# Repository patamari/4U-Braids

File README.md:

4U port of Braids, hardware is CC-by-SA 3.0.

C24 should be a good bipolar 10uF electrolytic cap.

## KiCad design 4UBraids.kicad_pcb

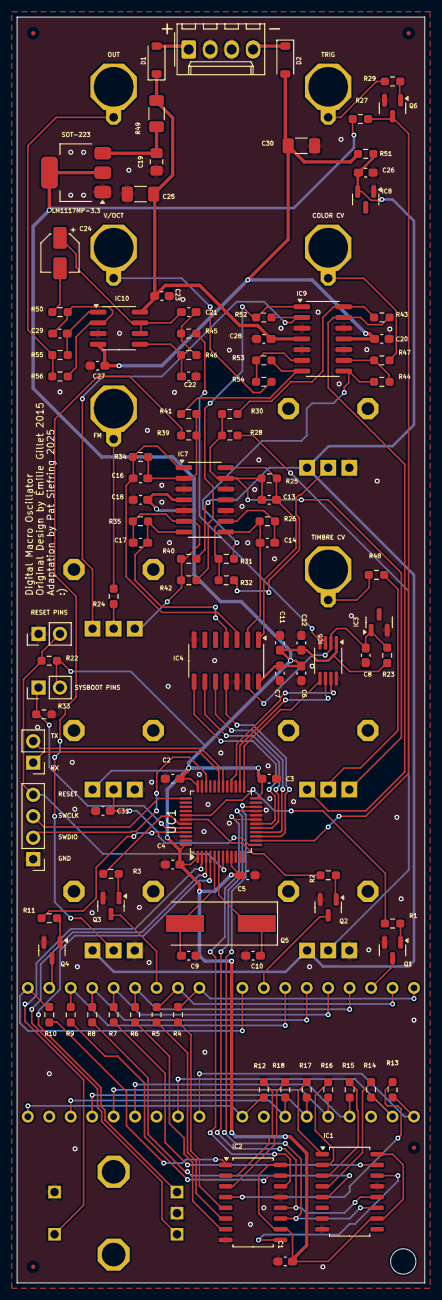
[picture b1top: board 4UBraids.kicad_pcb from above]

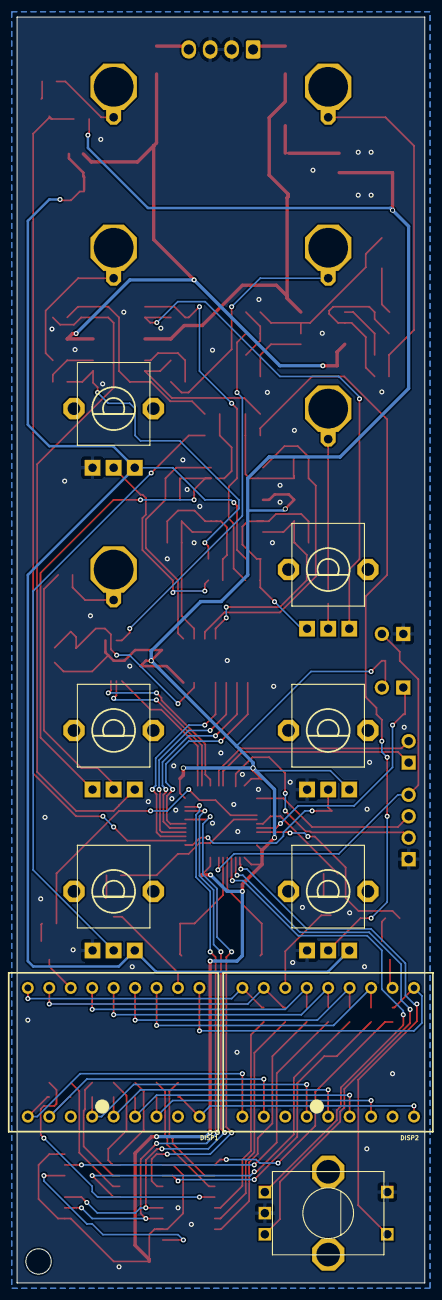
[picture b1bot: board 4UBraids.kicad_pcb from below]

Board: 2 copper layers, 48.3 x 149.9 mm, 108 parts (9 on the bottom side), 97 nets.

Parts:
C1, C2, C3, C4, C5, C7, C11, C18, C20, C23, C26, C27, C28, C31: 100n; C_0603_1608Metric_Pad1.08x0.95mm_HandSolder
C6, C12: 1u; C_0603_1608Metric_Pad1.08x0.95mm_HandSolder
C8: 470n; C_0603_1608Metric_Pad1.08x0.95mm_HandSolder
C9, C10: 18p; C_0603_1608Metric_Pad1.08x0.95mm_HandSolder
C13, C14, C16, C17: 1n; C_0603_1608Metric_Pad1.08x0.95mm_HandSolder
C19: 22uF; C_0805_2012Metric_Pad1.18x1.45mm_HandSolder
C21, C22: 100p; C_0603_1608Metric_Pad1.08x0.95mm_HandSolder
C24: 10u; CP_Elec_4x5.4
C25, C30: 47uF; C_1206_3216Metric_Pad1.33x1.80mm_HandSolder
C29: 47p; C_0603_1608Metric_Pad1.08x0.95mm_HandSolder
D1, D2: 1N5819HW; D_SOD-123
DISP1, DISP2: KINGBRIGHT-PDC54-11; PDC54
IC1, IC2: 74HC595D; SOIC-16_4.55x10.3mm_P1.27mm
IC3: LM4040B25; SOT-23
IC4: MCP3204; SOIC-14_3.9x8.7mm_P1.27mm
IC5: DAC8551; MSOP-8_3x3mm_P0.65mm
IC7: MCP6004; SOIC-14_3.9x8.7mm_P1.27mm
IC8: LM4040B10; SOT-23
IC9: TL074D; SOIC-14_3.9x8.7mm_P1.27mm
IC10: TL072; SOIC-8_3.9x4.9mm_P1.27mm
LM1117MP-3.3: SOT-223
Q1, Q2, Q3, Q4, Q6: MMBT3904; SOT-23
Q5: 8MHz; Crystal_SMD_HC49-SD
R1, R2, R3, R11, R23, R55: 1.0k; R_0603_1608Metric_Pad0.98x0.95mm_HandSolder
R4, R5, R6, R7, R8, R9, R10, R12, R13, R14, R15, R16, R17, R18: 100; R_0603_1608Metric_Pad0.98x0.95mm_HandSolder
R19, R20, R21, R36, R37, R38: 10kB; ALPS_POT_VERTICAL_PS
R22, R27, R33: 10k; R_0603_1608Metric_Pad0.98x0.95mm_HandSolder
R24, R29, R47, R48, R54, R56: 100k; R_0603_1608Metric_Pad0.98x0.95mm_HandSolder
R25, R26: 49.9k; R_0603_1608Metric_Pad0.98x0.95mm_HandSolder
R28, R32, R40: 200k; R_0603_1608Metric_Pad0.98x0.95mm_HandSolder
R30, R31, R34, R35, R41, R42, R43, R44, R50, R52, R53: 24.9k; R_0603_1608Metric_Pad0.98x0.95mm_HandSolder
R39: 120k; R_0603_1608Metric_Pad0.98x0.95mm_HandSolder
R45, R46: 39k; R_0603_1608Metric_Pad0.98x0.95mm_HandSolder
R49: 4.7; R_1206_3216Metric_Pad1.30x1.75mm_HandSolder
R51: 330; R_0603_1608Metric_Pad0.98x0.95mm_HandSolder
SW1: EC12E_SW; ALPS_EC12E_SW
UC1: STM32F103CBT6; LQFP-48_7x7mm_P0.5mm

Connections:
+3V3: C1.1, C2.1, C3.1, C4.1, C5.1, C6.1, C7.1, C11.1, C12.1, C18.1, IC1.10, IC1.16, IC2.10, IC2.16, IC4.14, IC5.1, IC7.4, LM1117MP-3.3.2, LM1117MP-3.3.4, R19.P$1, R22.2, R23.1, R27.2, UC1.1, UC1.9, UC1.24, UC1.36, UC1.48
ADC_MISO: IC4.10, UC1.16
ADC_MOSI: IC4.9, UC1.17
ADC_SCK: IC4.11, UC1.15
ADC_SS: IC4.8, UC1.18
AREF: C8.1, IC3.1, IC4.13, IC5.2, R23.2
AREF_-10: C26.1, IC8.2, R20.P$1, R36.P$1, R38.P$1, R40.1, R51.2
AUDIO_OUT: IC5.3, IC5.4, R45.2
BOOT_FLASH: R33.2, UC1.44
DAC_MOSI: IC5.7, UC1.28
DAC_SCK: IC5.6, UC1.26
DAC_SS: IC5.5, UC1.25
DISP_CHAR0: R3.1, UC1.43
DISP_CHAR1: R11.1, UC1.45
DISP_CHAR2: R1.1, UC1.41
DISP_CHAR3: R2.1, UC1.42
DISP_EN: IC1.12, IC2.12, UC1.21
DISP_SCK: IC1.11, IC2.11, UC1.22
DISP_SER: IC2.14, UC1.19
ENC_A: SW1.B, UC1.3
ENC_B: SW1.A, UC1.4
ENC_CLICK: SW1.E, UC1.2
FINE_TUNE: C31.1, R19.P$2, UC1.13
FM_CV: C17.2, IC4.4, IC7.7, R35.2
GATE: Q6.3, R27.1, UC1.14
GND: C1.2, C2.2, C3.2, C4.2, C5.2, C6.2, C7.2, C8.2, C9.1, C10.1, C11.2, C12.2, C18.2, C19.2, C20.1, C22.2, C23.2, C25.2, C26.2, C27.1, C28.2, C30.2, C31.2, IC1.8, IC1.13, IC2.8, IC2.13, IC3.2, IC4.7, IC4.12, IC5.8, IC7.3, IC7.5, IC7.10, IC7.11, IC7.12, IC8.1, IC9.3, IC9.5, IC9.10, IC9.12, IC10.3, LM1117MP-3.3.1, Q1.2, Q2.2, Q3.2, Q4.2, Q6.2, R19.P$3, R20.P$3, R33.1, R36.P$3, R38.P$3, SW1.C, SW1.D, UC1.8, UC1.20, UC1.23, UC1.35, UC1.46, UC1.47
unnamed: DISP2.16, Q3.3
unnamed: DISP2.11, Q4.3
unnamed: DISP1.16, Q1.3
unnamed: DISP1.11, Q2.3
unnamed: Q3.1, R3.2
unnamed: Q4.1, R11.2
unnamed: C9.2, Q5.2, UC1.5
unnamed: C10.2, Q5.1, UC1.6
unnamed: Q1.1, R1.2
unnamed: Q2.1, R2.2
unnamed: IC9.7, R41.1, R53.2
unnamed: R20.P$2, R39.1
unnamed: DISP1.12, DISP2.12, R9.2
unnamed: DISP1.10, DISP2.10, R10.2
unnamed: DISP1.9, DISP2.9, R12.2
unnamed: DISP1.7, DISP2.7, R18.2
unnamed: DISP1.1, DISP2.1, R13.2
unnamed: DISP1.18, DISP2.18, R4.2
unnamed: DISP1.17, DISP2.17, R5.2
unnamed: DISP1.15, DISP2.15, R6.2
unnamed: DISP1.14, DISP2.14, R7.2
unnamed: DISP1.6, DISP2.6, R17.2
unnamed: DISP1.5, DISP2.5, R16.2
unnamed: DISP1.4, DISP2.4, R15.2
unnamed: DISP1.2, DISP2.2, R14.2
unnamed: DISP1.13, DISP2.13, R8.2
unnamed: C16.1, IC7.2, R34.1, R39.2, R41.2
unnamed: IC2.7, R6.1
unnamed: IC1.14, IC2.9
unnamed: IC2.15, R9.1
unnamed: IC2.1, R10.1
unnamed: IC2.2, R12.1
unnamed: IC2.3, R18.1
unnamed: IC2.4, R13.1
unnamed: IC2.5, R4.1
unnamed: IC2.6, R5.1
unnamed: IC1.15, R7.1
unnamed: IC1.1, R17.1
unnamed: IC1.2, R16.1
unnamed: IC1.3, R15.1
unnamed: IC1.4, R14.1
unnamed: IC1.5, R8.1
unnamed: IC9.6, R53.1, R54.2
unnamed: R21.P$2, R24.2
unnamed: C19.1, LM1117MP-3.3.3, R49.1
unnamed: IC9.13, R37.P$1, R43.1
unnamed: IC9.14, R30.1, R43.2
unnamed: IC9.2, R21.P$1, R52.1
unnamed: IC9.1, R42.1, R52.2
unnamed: C17.1, IC7.6, R21.P$3, R35.1, R40.2, R42.2
unnamed: IC9.8, R31.1, R44.2
unnamed: C13.1, IC7.13, R25.1, R28.2, R30.2, R37.P$3
unnamed: R28.1, R36.P$2
unnamed: R37.P$2, R48.2
unnamed: IC9.9, R44.1, R47.2
unnamed: R32.1, R38.P$2
unnamed: Q6.1, R29.2
unnamed: C21.2, C24.1, IC10.6, IC10.7
unnamed: C24.2, R50.2
unnamed: C22.1, IC10.5, R46.1
unnamed: C14.1, IC7.9, R26.1, R31.2, R32.2
unnamed: C21.1, R45.1, R46.2
unnamed: R55.1, R56.1
unnamed: C29.2, IC10.1, R55.2
unnamed: C29.1, IC10.2, R50.1, R56.2
PARAM1_CV: C13.2, IC4.1, IC7.14, R25.2
PARAM2_CV: C14.2, IC4.2, IC7.8, R26.2
PITCH_CV: C16.2, IC4.3, IC7.1, R34.2
RESET: R22.1, UC1.7
VCC: C23.1, C25.1, C28.1, D1.1, IC9.4, IC10.8, R49.2
VEE: C20.2, C27.2, C30.1, D2.2, IC9.11, IC10.4, R51.1
